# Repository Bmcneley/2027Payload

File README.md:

# 2027Payload
KiCad project files for 2027 Cy Launch payload PCB.

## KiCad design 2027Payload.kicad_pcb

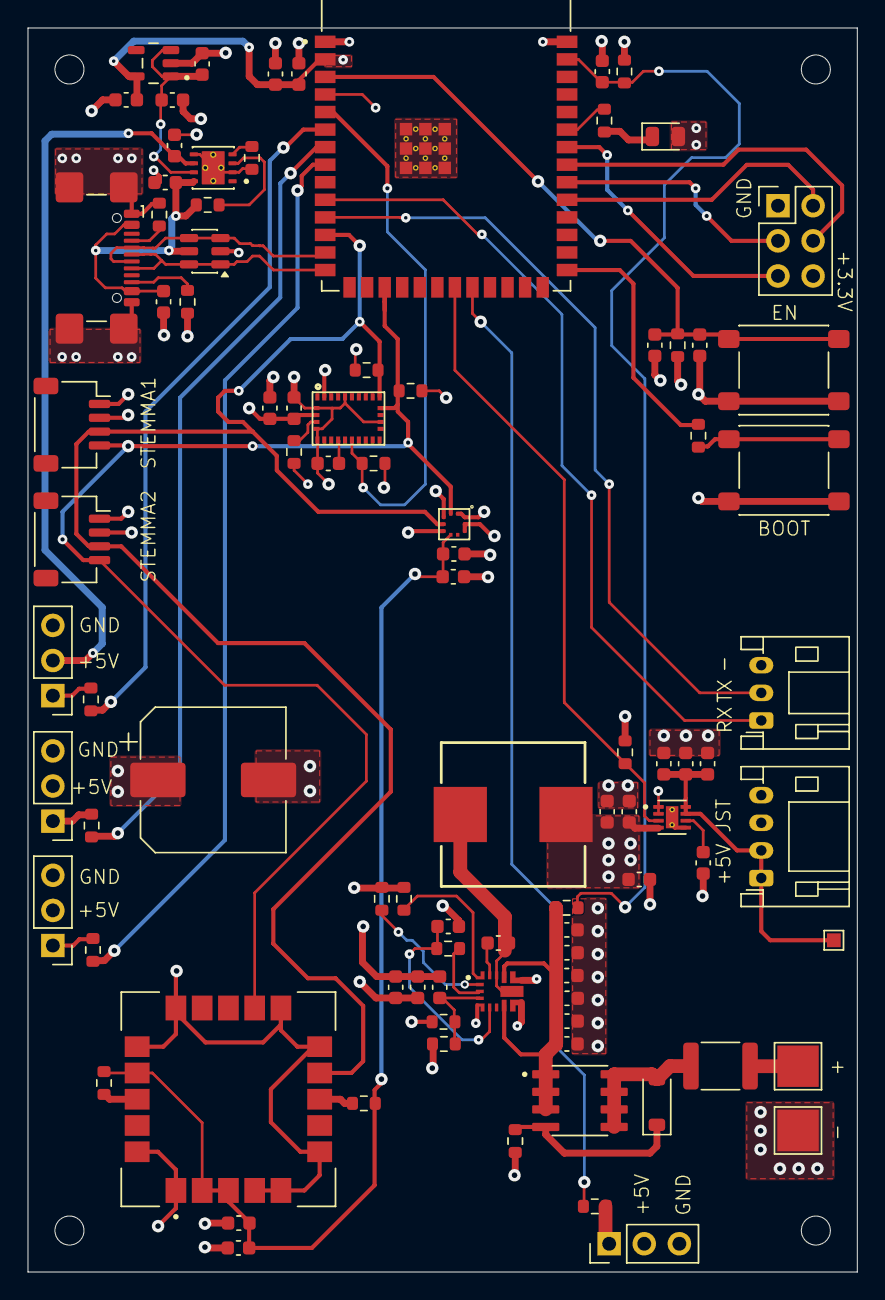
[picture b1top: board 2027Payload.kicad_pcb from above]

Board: 4 copper layers, 60.0 x 90.0 mm, 96 parts (0 on the bottom side), 52 nets.

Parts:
C2: 470u; CP_Elec_10x10
C5, C14, C27, C29: 10u; C_0603_1608Metric
C12, C13, C15, C16, C17: 1u; C_0603_1608Metric
C18, C23, C24, C25, C26, C28, C31, C34, C47, C48, C49: 100n; C_0603_1608Metric
C22, C42, C43, C45: 0.1u; C_0603_1608Metric
C30, C32, C33, C37, C38: 4.7u; C_0603_1608Metric
C35: 15p; C_0603_1608Metric
C36, C39: 47u; C_0603_1608Metric
C40, C41, C44: 22u; C_0603_1608Metric
C46: 10n; C_0603_1608Metric
D1: LED; LED_0805_2012Metric
D2: 10V; D_SOD-123
F1: 5A; Fuse_1812_4532Metric
H1, H2, H3, H4: MountingHole; MountingHole_2.1mm
J1: USB_C_Receptacle_USB2.0_16P; USB_C_Receptacle_GCT_USB4110
J2, J9: Conn_01x01; TestPoint_Pad_3.0x3.0mm
J3, J4, J5, J12: Conn_01x03; PinHeader_1x03_P2.54mm_Vertical
J6, J7: Conn_01x04; JST_SH_SM04B-SRSS-TB_1x04-1MP_P1.00mm_Horizontal
J8: Conn_01x04; JST_PH_S4B-PH-K_1x04_P2.00mm_Horizontal
J10: Conn_02x03_Odd_Even; PinHeader_2x03_P2.54mm_Vertical
J11: Conn_01x03; JST_PH_S3B-PH-K_1x03_P2.00mm_Horizontal
L1: 2.4uH; WE-HCI_1050
Q2: AO4407A; SOIC127P600X175-8N
R7, R8: 5.1K; R_0603_1608Metric
R9, R24, R27, R28, R29, R35, R38, R39, R40: 10k; R_0603_1608Metric
R10: 100R; R_0603_1608Metric
R15: 332R; R_0603_1608Metric
R16: 91k; R_0603_1608Metric
R21, R22, R36: 100k; R_0603_1608Metric
R23: 43k; R_0603_1608Metric
R25: 11.3k; R_0603_1608Metric
R26: 24.3k; R_0603_1608Metric
R30, R32, R33, R37: 330R; R_0603_1608Metric
R31: 300R; R_0603_1608Metric
R34: 90.9k; R_0603_1608Metric
SW1, SW2: SW_Push; SW_SPST_PTS645Sx43SMTR92
TP1: TestPoint; TestPoint_Pad_1.0x1.0mm
U1: ESP32-S3-WROOM-1-N8R8; XCVR_ESP32S3WROOM1N8R8
U2: TPS543620RPYR; IC_TPS543620RPYR
U3: TPS22965DSGT; SON50P200X200X80-9N
U5: BNO055; LGA28R50P4X10_380X520X100
U6: USBLC6-2SC6; SOT-23-6
U7: TLV75533PDBVR; SOT95P280X145-5N
U9: TPS2113ADRBR; SON65P300X300X100-9N
U11: SAM-M10Q-00B; XCVR_SAM-M10Q-00B
U12: BMP581

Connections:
5V_LOGIC: C14.1, C15.2, U7.1 (IN), U7.3 (EN), U9.7 (OUT)
5V_SW: C41.1, C44.1, C45.1, J8.1, J8.2, TP1.1 (1_1), U3.7 (VOUT_7), U3.8 (VOUT_8)
+3.3V: C5.1, C16.2, C22.1, C24.1, C25.1, C27.1, C28.1, C47.1, C48.1, J6.2, J7.2, J10.6, R9.1, R27.1, R28.1, R29.1, R38.1, R39.1, R40.1, U1.2 (3V3), U5.3 (VDD), U5.28 (VDDIO), U7.5 (OUT), U11.2 (V_IO), U11.3 (V_BCKP), U11.17 (VCC), U12.1 (VDDIO), U12.6 (CSB), U12.10 (VDD)
+5V: C2.1, C13.1, C35.2, C36.2, C39.2, C40.1, C42.1, C43.1, J3.2, J4.2, J5.2, J12.2, L1.2, R34.2, U3.1 (VIN_1), U3.2 (VIN_2), U3.4 (VBIAS), U9.6 (IN2)
/CC1: J1.A5 (CC1), R7.1
/CC2: J1.B5 (CC2), R8.1
D+: J1.A6 (D+), J1.B6 (D+), U1.14 (IO20), U6.1 (I/O1), U6.6 (I/O1)
D-: J1.A7 (D-), J1.B7 (D-), U1.13 (IO19), U6.3 (I/O2), U6.4 (I/O2)
EN: C17.2, C18.1, R9.2, SW1.1, U1.3 (EN)
GND: C2.2, C5.2, C12.1, C13.2, C14.2, C15.1, C16.1, C17.1, C18.2, C22.2, C23.2, C24.2, C25.2, C26.2, C27.2, C28.2, C29.2, C30.2, C31.2, C32.2, C33.2, C36.1, C37.2, C38.2, C39.1, C40.2, C41.2, C42.2, C43.2, C44.2, C45.2, C46.2, C47.2, C48.2, C49.2, D1.2 (A), J1.A1 (GND), J1.A12 (GND), J1.B1 (GND), J1.B12 (GND), J1.SH (SHIELD), J3.3, J4.3, J5.3, J6.1, J7.1, J8.3, J8.4, J9.1 (Pin_1_1), J10.1, J11.3, J12.3, R7.2, R8.2, R15.2, R21.2, R23.1, R25.2, R26.2, R35.1, R36.1, SW1.2, SW2.2, U1.1 (GND), U1.40 (GND), U1.41_1 (GND), U1.41_2 (GND), U1.41_3 (GND), U1.41_4 (GND), U1.41_5 (GND), U1.41_6 (GND), U1.41_7 (GND), U1.41_8 (GND), U1.41_9 (GND), U2.5 (AGND), U2.9 (PGND), U2.11 (PGND__1), U3.5 (GND), U3.9 (EXP), U5.2 (GND), U5.5 (PS1), U5.6 (PS0), U5.17 (COM3), U5.25 (GNDIO), U6.2 (GND), U7.2 (GND), U9.2 (~EN), U9.5 (GND), U9.9 (GND), U11.1 (GND), U11.4 (GND), U11.5 (GND), U11.6 (GND), U11.10 (GND), U11.11 (GND), U11.15 (GND), U11.16 (GND), U11.20 (GND), U12.3 (GND), U12.5 (SDO/ADR), U12.8 (GND), U12.9 (GND)
IO0: R10.2, U1.27 (IO0)
IO1: C23.1, R22.2, R23.2, U1.39 (IO1)
IO5: R29.2, U1.5 (IO5), U5.11 (NRESET)
IO6: R30.2, U1.6 (IO6)
IO7: R32.2, U1.7 (IO7)
IO8: J6.3, J7.3, R39.2, U1.12 (IO8), U5.20 (COM0), U11.9 (SDA), U12.4 (SDI/SDA)
IO9: J6.4, J7.4, R40.2, U1.17 (IO9), U5.19 (COM1), U11.12 (SCL), U12.2 (SCK/SCL)
IO13: R36.2, U1.21 (IO13), U3.3 (ON)
IO14: R37.2, U1.22 (IO14)
IO15: R33.2, U1.8 (IO15)
IO17: J11.1, U1.10 (IO17)
IO18: J11.2, U1.11 (IO18)
IO38: J10.2, U1.31 (IO38)
IO39: J10.3, U1.32 (IO39)
IO40: J10.4, U1.33 (IO40)
IO41: J10.5, U1.34 (IO41)
IO42: R31.2, U1.35 (IO42)
unnamed: D1.1 (K), R31.1
unnamed: D2.1 (K), Q2.4, R21.1
unnamed: J3.1, R30.1
unnamed: J4.1, R32.1
unnamed: J5.1, R33.1
unnamed: J12.1, R37.1
unnamed: R10.1, SW2.1
unnamed: C34.1, U2.14 (BOOT)
unnamed: C33.1, R24.2, U2.6 (BP5)
unnamed: C35.1, R34.1, R35.2, U2.4 (FB)
unnamed: R25.1, U2.2 (MODE)
unnamed: R24.1, U2.3 (PGOOD)
unnamed: C34.2, L1.1, U2.10 (SW1), U2.13 (SW2)
unnamed: R26.1, U2.1 (SYNC/FSEL)
unnamed: C46.1, U3.6 (CT)
unnamed: C49.1, U5.9 (CAP)
unnamed: R38.2, U5.4 (NBOOT_LOAD_PIN)
unnamed: R15.1, U9.4 (ILIM)
unnamed: R27.2, U11.18 (~RESET)
unnamed: R28.2, U11.8 (~SAFEBOOT)
VBAT: C26.1, C30.1, C31.1, C32.1, C37.1, C38.1, Q2.1, Q2.2, Q2.3, R22.1, U2.8 (VIN), U2.12 (VIN__1)
VBAT_FUSED: D2.2 (A), F1.2, Q2.5, Q2.6, Q2.7, Q2.8
VBAT_RAW: F1.1, J2.1 (Pin_1_1)
VBUS: C12.2, C29.1, J1.A4 (VBUS), J1.A9 (VBUS), J1.B4 (VBUS), J1.B9 (VBUS), R16.2, U6.5 (VBUS), U9.8 (IN1)
VSNS: R16.1, U9.3 (VSNS)

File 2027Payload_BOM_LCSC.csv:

Quantity,Manufacture Part Number,Manufacturer,Package,Description,Designator,LCSC Part Number,Notes
1,ESP32-S3-WROOM-1-N8R8,Espressif,Module,"ESP32-S3 WiFi/BLE module, 8MB flash + 8MB PSRAM",U1,C2913201,
1,TPS543620RPYR,Texas Instruments,VQFN-15 (RPY),"6A synchronous buck converter, 4-18V in",U2,,Not stocked at LCSC as of this writing - DigiKey/Mouser
1,TPS22965DSGT,Texas Instruments,WSON-8-EP 2x2,"Load switch, 5.7V 6A, adj. slew rate",U3,C347592,
1,BNO085,CEVA / Hillcrest,LGA-28,9-DOF IMU with sensor fusion,U4,C5189642,
1,USBLC6-2SC6,STMicroelectronics,SOT-23-6,USB 2.0 ESD protection array,U6,C7519,
1,TLV75533PDBVR,Texas Instruments,SOT-23-5,3.3V 500mA LDO,U7,C404027,
1,TPS2113ADRBR,Texas Instruments,VSON-8 (DRB),"Autoswitching power mux, 2.8-5.5V",U9,C354512,
1,SAM-M10Q-00B,u-blox,Module 15.5x15.5,GNSS module with integrated patch antenna,U11,C5443880,
1,BMP581,Bosch Sensortec,LGA-10,Barometric pressure sensor,U12,C5362283,
1,AO4407A,Alpha & Omega,SOIC-8,"P-channel MOSFET -30V -12A, reverse polarity protection",Q2,C16072,
1,BZT52C10,Various (e.g. Changjiang),SOD-123,"10V zener, 500mW - Q2 gate clamp",D2,,Verify value/type from your symbol; MMSZ5240B is an equivalent
1,KT-0603G,Hubei KENTO,0603,"Green LED, 20mA",D1,,Any 0603 LED; pick colour you want
1,SWPA6045S2R2MT,Sunlord,6.0x6.0x4.5mm,"2.2uH shielded power inductor, 6.4A Isat",L1,,Schematic says 2.4uH - 2.2uH is nearest standard. Needs Isat > 8A ideally
1,0603SFH500F/32-2,Bel Fuse,1206,5A fast-acting SMD fuse,F1,,Or a 5A polyfuse / blade holder depending on your footprint
1,TYPE-C-31-M-12,Korean Hroparts Elec,SMD 16P,"USB Type-C receptacle, USB 2.0, 16 pin",J1,C165948,
2,SM04B-SRSS-TB(LF)(SN),JST,SH 1.0mm 4P side entry,STEMMA QT / Qwiic connector,"J6,J7",C160404,
1,B4B-XH-A(LF)(SN),JST,XH 2.5mm 4P THT,5V JST power connector,J8,C144395,Swap to S4B-XH-SM4-TB (C161861) if you want SMD
4,PH1-03-UA,Ckmtw,2.54mm 1x3 header,3-pin male header - servo x3 + UART,"J3,J4,J5,J11",,Cut from a strip; 1x40 strip is cheaper
1,PZ254V-11-06P,Ckmtw,2.54mm 2x3 header,"2x3 male header, GPIO breakout",J10,,
2,,,Solder pad,VBAT_RAW / VBAT_FUSED test pads - no part to buy,"J2,J9",,Do not populate
2,TS-1187A-B-A-B,XKB Connection,SMD 3x4x2mm,Tactile push button - BOOT / EN,"SW1,SW2",C318884,
1,,,Pad,Test point 5V_SW - no part to buy,TP1,,Do not populate
4,,,M3,Mounting hole - no part to buy,"H1,H2,H3,H4",,Do not populate
2,RC0603FR-075K1L,YAGEO,0603,5.1k 1% 1/10W - USB-C CC pulldowns,"R7,R8",,
9,RC0603FR-0710KL,YAGEO,0603,10k 1% 1/10W - pullups / PGOOD / feedback network,"R9,R14,R19,R20,R24,R27,R28,R29,R35",,
2,RC0603FR-074K7L,YAGEO,0603,4.7k 1% 1/10W - I2C pullups,"R17,R18",,
1,RC0603FR-07100RL,YAGEO,0603,100R 1% 1/10W - IO0 series,R10,,
1,RC0603FR-07332RL,YAGEO,0603,332R 1% 1/10W - TPS2113A ILIM,R15,,
1,RC0603FR-0791KL,YAGEO,0603,91k 1% 1/10W,R16,,
3,RC0603FR-07100KL,YAGEO,0603,100k 1% 1/10W,"R21,R22,R36",,
1,RC0603FR-0743KL,YAGEO,0603,43k 1% 1/10W - VBAT sense divider,R23,,
1,RC0603FR-0711K3L,YAGEO,0603,11.3k 1% 1/10W - buck FB divider bottom,R25,,
1,RC0603FR-0724K3L,YAGEO,0603,24.3k 1% 1/10W - buck FB divider top,R26,,
3,RC0603FR-07330RL,YAGEO,0603,330R 1% 1/10W - servo signal series,"R30,R32,R33",,
1,RC0603FR-07300RL,YAGEO,0603,300R 1% 1/10W - status LED,R31,,
1,RC0603FR-0790K9L,YAGEO,0603,90.9k 1% 1/10W,R34,,
15,CL10B104KB8NNNC,Samsung,0603,100nF 50V X7R - decoupling,"C18,C19,C20,C21,C22,C23,C24,C25,C26,C28,C31,C34,C42,C43,C45",,
5,CL10B105KB8NNNC,Samsung,0603,1uF 50V X7R,"C12,C13,C15,C16,C17",,
1,CL10B103KB8NNNC,Samsung,0603,10nF 50V X7R - TPS22965 CT slew rate,C46,,
1,CL10C150JB8NNNC,Samsung,0603,15pF 50V C0G - buck BOOT/FB,C35,,
5,CC0603KRX5R8BB475,YAGEO,0603,"4.7uF 25V X5R 10% - buck input bank (VBAT, 8.4V max)","C30,C32,C33,C37,C38",C326580,~2.7uF each after DC bias at 8.4V; 5 in parallel is still fine for the TPS543620 input
4,GRM188R61E106MA73D,Murata,0603,10uF 25V X5R - VBUS / 5V_LOGIC / 3V3 / GPS VCC,"C5,C14,C27,C29",C91606,25V rating keeps most of the capacitance at 3.3-5V
3,GRT188R61A226ME13D,Murata,0603,22uF 10V X5R - load switch input + 5V_SW output bulk,"C40,C41,C44",C126630,Was 220uF/22uF/100uF. ~10uF effective each at 5V. Beats a 47uF/6.3V 0603 here - less DC bias derating despite the lower nominal
2,GRM188R60J476ME01D,Murata,0603,47uF 6.3V X5R - buck output,"C36,C39",C3848273,~8uF each after DC bias at 5V (~16uF total vs 94uF nominal). This pair matters more than C40/C44 for Pi load steps - consider 1210 here if you change any footprint
1,RVT1E471M1010,ROQANG,CP_Elec_10x10,470uF 25V aluminium electrolytic - +5V servo rail bulk,C2,C72518,
